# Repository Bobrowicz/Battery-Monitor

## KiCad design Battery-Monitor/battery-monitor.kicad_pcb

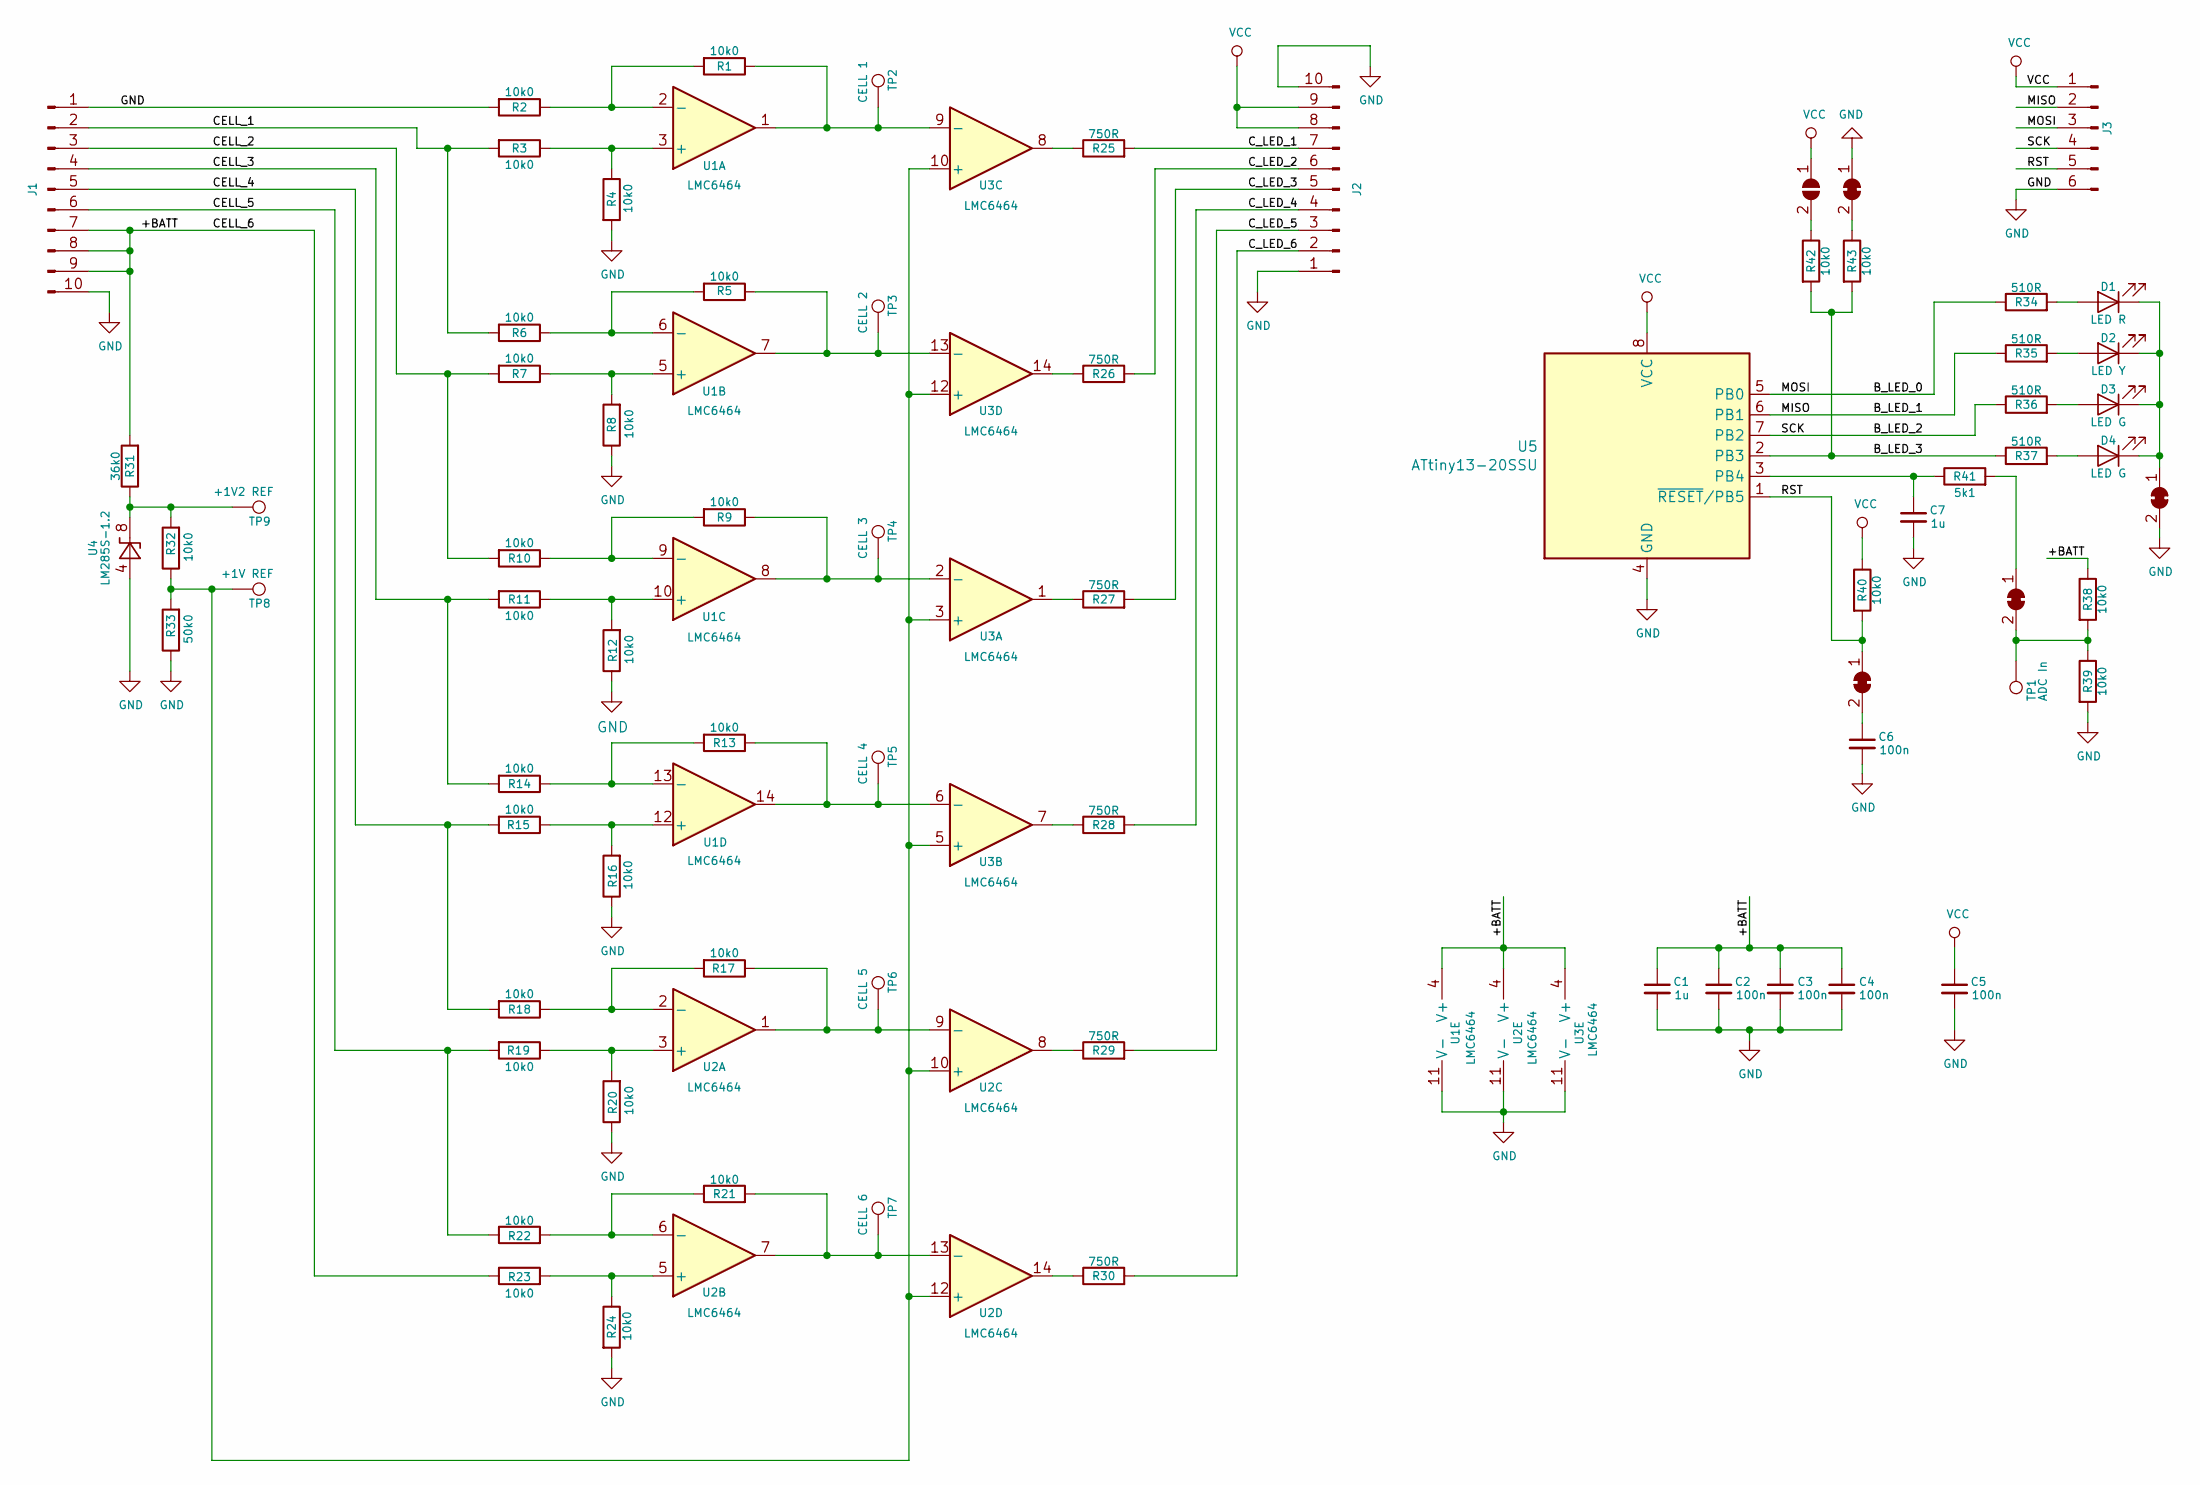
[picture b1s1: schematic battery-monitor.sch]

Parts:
C1, C7: 1u; C_0805_HandSoldering
C2, C3, C4, C5, C6: 100n; C_0805_HandSoldering
D1: LED R; LED_0805_HandSoldering
D2: LED Y; LED_0805_HandSoldering
D3, D4: LED G; LED_0805_HandSoldering
J1, J2: Conn_01x10_Male; Pin_Header_Straight_1x10_Pitch2.54mm
J3: Conn_01x06_Male; Pin_Header_Straight_1x06_Pitch2.54mm
JP1: SolderJumper_2_Open; SolderJumper-2_P1.3mm_Open_Pad1.0x1.5mm
JP2, JP3, JP4, JP5: SolderJumper_2_Bridged; SolderJumper-2_P1.3mm_Bridged_Pad1.0x1.5mm
R1, R2, R3, R4, R5, R6, R7, R8, R9, R10, R11, R12, R13, R14, R15, R16, R17, R18, R19, R20, R21, R22, R23, R24: 10k0; R_0603_HandSoldering
R25, R26, R27, R28, R29, R30: 750R; R_0603_HandSoldering
R31: 36k0; R_0805_HandSoldering
R32, R38, R39, R40, R42, R43: 10k0; R_0805_HandSoldering
R33: 50k0; R_0805_HandSoldering
R34, R35, R36, R37: 510R; R_0805_HandSoldering
R41: 5k1; R_0805_HandSoldering
TP1: ADC In; Measurement_Point_Round-SMD-Pad_Small
TP2: CELL 1; Measurement_Point_Round-SMD-Pad_Small
TP3: CELL 2; Measurement_Point_Round-SMD-Pad_Small
TP4: CELL 3; Measurement_Point_Round-SMD-Pad_Small
TP5: CELL 4; Measurement_Point_Round-SMD-Pad_Small
TP6: CELL 5; Measurement_Point_Round-SMD-Pad_Small
TP7: CELL 6; Measurement_Point_Round-SMD-Pad_Small
TP8: +1V REF; Measurement_Point_Round-SMD-Pad_Small
TP9: +1V2 REF; Measurement_Point_Round-SMD-Pad_Small
U1, U2, U3: LMC6464; SOIC-14_N
U4: LM285S-1.2; SOIC-8-N
U5: ATtiny13-20SSU; SOIC-8-N

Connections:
/+BATT: C1.1, C2.1, C3.1, C4.1, J1.7, J1.8, J1.9, R23.1, R31.2, R38.1, U1.4 (V+), U2.4 (V+), U3.4 (V+)
/B_LED_0: J3.3, R34.1, U5.5 (PB0)
/B_LED_1: J3.2, R35.1, U5.6 (PB1)
/B_LED_2: J3.4, R36.1, U5.7 (PB2)
/B_LED_3: R37.1, R42.2, R43.2, U5.2 (PB3)
/CELL_1: J1.2, R3.2, R6.2
/CELL_2: J1.3, R7.2, R10.2
/CELL_3: J1.4, R11.2, R14.2
/CELL_4: J1.5, R15.2, R18.2
/CELL_5: J1.6, R19.2, R22.1
/C_LED_1: J2.7, R25.2
/C_LED_2: J2.6, R26.2
/C_LED_3: J2.5, R27.2
/C_LED_4: J2.4, R28.2
/C_LED_5: J2.3, R29.2
/C_LED_6: J2.2, R30.2
/RST: J3.5, JP5.1 (A), R40.2, U5.1 (~RESET~/PB5)
GND: C1.2, C2.2, C3.2, C4.2, C5.2, C6.2, C7.2, J1.1, J1.10, J2.1, J2.10, J3.6, JP2.1 (A), JP4.2 (B), R2.2, R4.2, R8.1, R12.1, R16.1, R20.1, R24.2, R33.1, R39.2, U1.11 (V-), U2.11 (V-), U3.11 (V-), U4.4 (A), U5.4 (GND)
unnamed: C6.1, JP5.2 (B)
unnamed: C7.1, R41.1, U5.3 (PB4)
unnamed: D1.1 (K), D2.1 (K), D3.1 (K), D4.1 (K), JP4.1 (A)
unnamed: D1.2 (A), R34.2
unnamed: D2.2 (A), R35.2
unnamed: D3.2 (A), R36.2
unnamed: D4.2 (A), R37.2
unnamed: JP1.2 (B), R42.1
unnamed: JP2.2 (B), R43.1
unnamed: JP3.1 (A), R41.2
unnamed: JP3.2 (B), R38.2, R39.1, TP1.1
unnamed: R1.1, TP2.1, U1.1, U3.9 (-)
unnamed: R1.2, R2.1, U1.2 (-)
unnamed: R3.1, R4.1, U1.3 (+)
unnamed: R5.1, TP3.1, U1.7, U3.13 (-)
unnamed: R5.2, R6.1, U1.6 (-)
unnamed: R7.1, R8.2, U1.5 (+)
unnamed: R9.1, TP4.1, U1.8, U3.2 (-)
unnamed: R9.2, R10.1, U1.9 (-)
unnamed: R11.1, R12.2, U1.10 (+)
unnamed: R13.1, TP5.1, U1.14, U3.6 (-)
unnamed: R13.2, R14.1, U1.13 (-)
unnamed: R15.1, R16.2, U1.12 (+)
unnamed: R17.1, TP6.1, U2.1, U2.9 (-)
unnamed: R17.2, R18.1, U2.2 (-)
unnamed: R19.1, R20.2, U2.3 (+)
unnamed: R21.1, R22.2, U2.6 (-)
unnamed: R21.2, TP7.1, U2.7, U2.13 (-)
unnamed: R23.2, R24.1, U2.5 (+)
unnamed: R25.1, U3.8
unnamed: R26.1, U3.14
unnamed: R27.1, U3.1
unnamed: R28.1, U3.7
unnamed: R29.1, U2.8
unnamed: R30.1, U2.14
unnamed: R31.1, R32.2, TP9.1, U4.6 (K), U4.8 (K)
unnamed: R32.1, R33.2, TP8.1, U2.10 (+), U2.12 (+), U3.3 (+), U3.5 (+), U3.10 (+), U3.12 (+)
VCC: C5.1, J2.8, J2.9, J3.1, JP1.1 (A), R40.1, U5.8 (VCC)

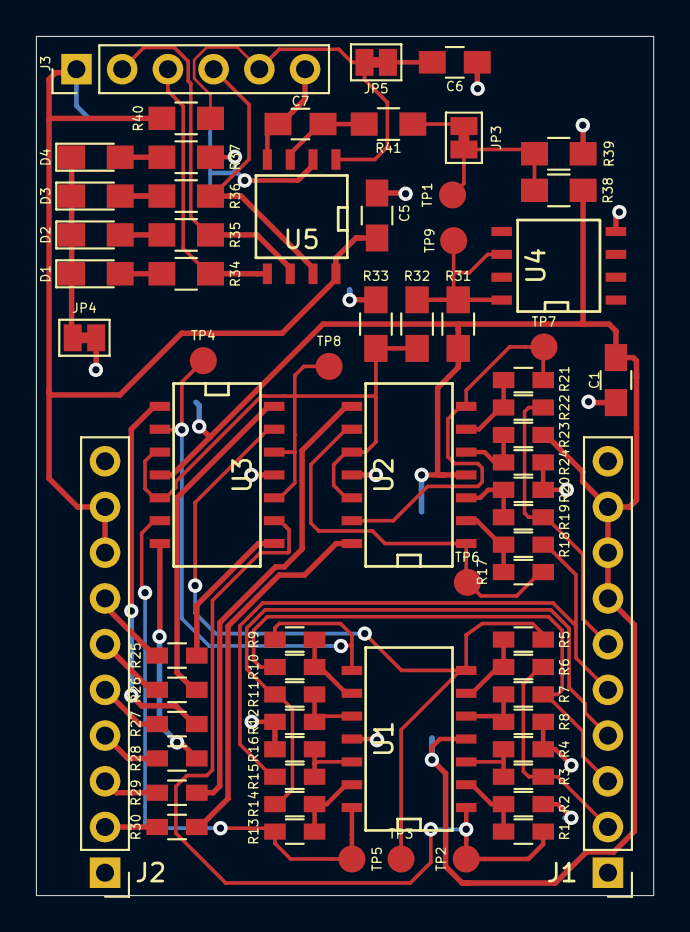
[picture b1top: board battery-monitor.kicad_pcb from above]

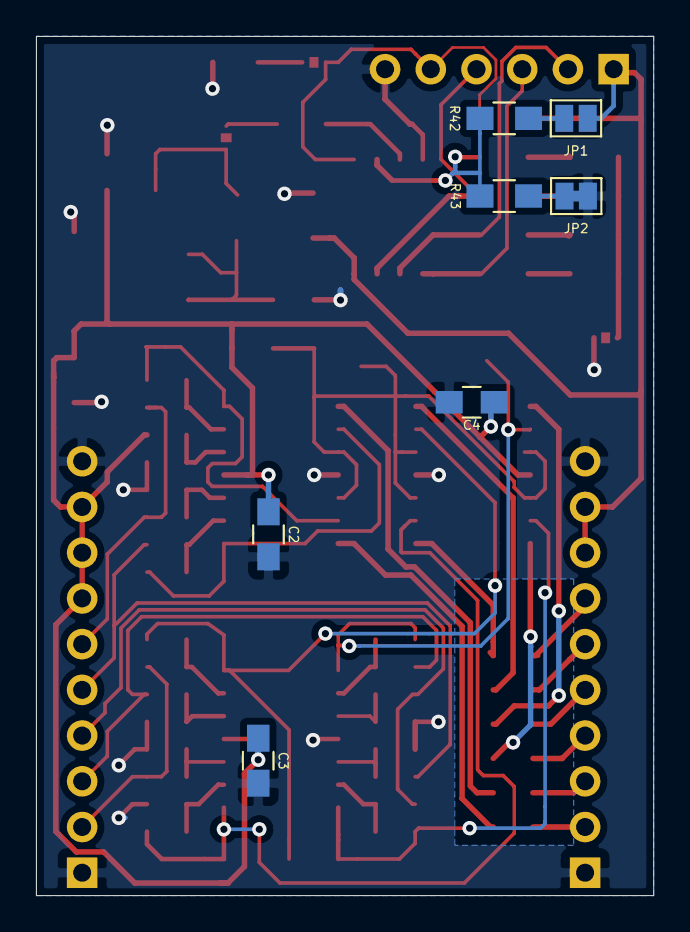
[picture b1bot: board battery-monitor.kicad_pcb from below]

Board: 2 copper layers, 34.3 x 47.7 mm, 76 parts (7 on the bottom side), 56 nets.

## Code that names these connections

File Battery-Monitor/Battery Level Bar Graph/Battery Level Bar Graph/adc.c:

/*
 * adc.c
 *
 * Created: 4/11/2019 8:01:28 PM
 *  Author: peter
 */ 

 #include <adc.h>

 /* Initialize ADC */
 void adc_init()
 {	/* Voltage reference selection */
	 //ADMUX |= (1 << REFS0);	// Enabled: 1.1V internal voltage reference
	 // Disabled: Vcc as reference

	 /* Presentation of the ADC results in ADC Data Register */
	 //ADMUX |= (1 << ADLAR);	// Enabled: left adjusted result
	 // Disabled: right adjusted result

	 /* Input channel selection */
	 ADMUX |= 
	 //0x00;			// ADC0 (PB5)
	 //0x01;			// ADC1 (PB2)
	 //0x02;		    // ADC2 (PB4)
	 0x03;			 // ADC3 (PB3)

	 /* ADC Enable */
	 ADCSRA |= (1 << ADEN);

	 /* ADC Auto Trigger Enable */
	 //ADCSRA |= (1<< ADATE);

	 /* ADC Interrupt Enable */
	 //ADCSRA |= (1 << ADIE);

	 /* ADC prescaler selections */
	 ADCSRA |=   
	 /*0x00;*/		// div 2
	 /*0x01;*/		// div 2
	 /*0x02;*/		// div 4
	 /*0x03;*/		// div 8
	 0x04; 			// div 16
	 /*0x05;*/		// div 32
	 /*0x06;*/		// div 64
	 /*0x07;*/		// div 128
	 
	 /* ADC auto trigger sources */
	 //ADCSRB |=	/*0x00;*/		// Free Running Mode
	 /*0x01;*/		// Analog Comparator
	 /*0x02;*/		// External Interrupt Request 0
	 /*0x03;*/		// Timer/Counter Compare Match A
	 /*0x04;*/ 		// Timer/Counter Overflow
	 /*0x05;*/		// Timer/Counter Compare Match B
	 /*0x06;*/		// Pin Change Interrupt Request

	 /* Digital input disable */
	 //DIDR0 |= (1 << ADC0D);	// Disable Digital Input Buffer on ADC0
	 DIDR0 |= (1 << ADC2D);		// Disable Digital Input Buffer on ADC2
	 //DIDR0 |= (1 << ADC3D);	// Disable Digital Input Buffer on ADC3
	 //DIDR0 |= (1 << ADC1D);	// Disable Digital Input Buffer on ADC1
 }

 void adc_disable()
 {
	ADCSRA &= ~(1 << ADEN);
 }

 void adc_enable()
 {
	ADCSRA |= (1 << ADEN);
 }

 /* Perform single conversion and return result */
 uint16_t adc_read_single()
 {
	 ADCSRA |= (1 << ADSC);
	 while(bit_is_set(ADCSRA, ADSC));
	 return ADCW;
 }

 void adc_select_channel(uint8_t channel)
 {
	ADMUX &= 0b11111100;
	ADMUX |= (0b00000011 & channel);
 }

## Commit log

2019-04-14 LED bar graph code for attiny13
2019-04-16 Circuit tweaks
    Added pull up/down resistor and solder bridge to allow mcu pick LED mode
    at startup. Added LPF to ADC input.
2019-04-26 begun pcb layout
2019-08-11 completed layoul
